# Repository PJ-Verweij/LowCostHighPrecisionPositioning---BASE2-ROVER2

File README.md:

# LowCostHighPrecisionPositioning - BASE2, ROVER2

Here you can find all 3D models (SolidWorks 2019), PCB designs (KiCad) and documentation for the BASE2 and ROVER2 which have been designed during the master thesis project of Peter Verweij. <br/><br/>

The aim of this project was to create a low cost high precision positioning system for Ghana. <br/>
The showcase and explanation of the project can be found in this [showcase movie](https://www.youtube.com/watch?v=F1svl4LCIXA&feature=youtu.be&ab_channel=PeterVerweij)<br/><br/>

For the Ublox GNSS receiver configuration I refer to the work of hcwinsemius and kriete on the [RTK_GNSS github page](https://github.com/hcwinsemius/RTK_GNSS)<br/><br/>

Finally, the files and explanation to add a GPRS cellular connection to the raspberry PI can be found here aswell.<br/><br/>

It has to be noted that this project is in a prototype state. There is still a lot to be desired. For example: the custom PCBs connect prototype breakoutboards, there are no indicator lights in the devices, etcetera.

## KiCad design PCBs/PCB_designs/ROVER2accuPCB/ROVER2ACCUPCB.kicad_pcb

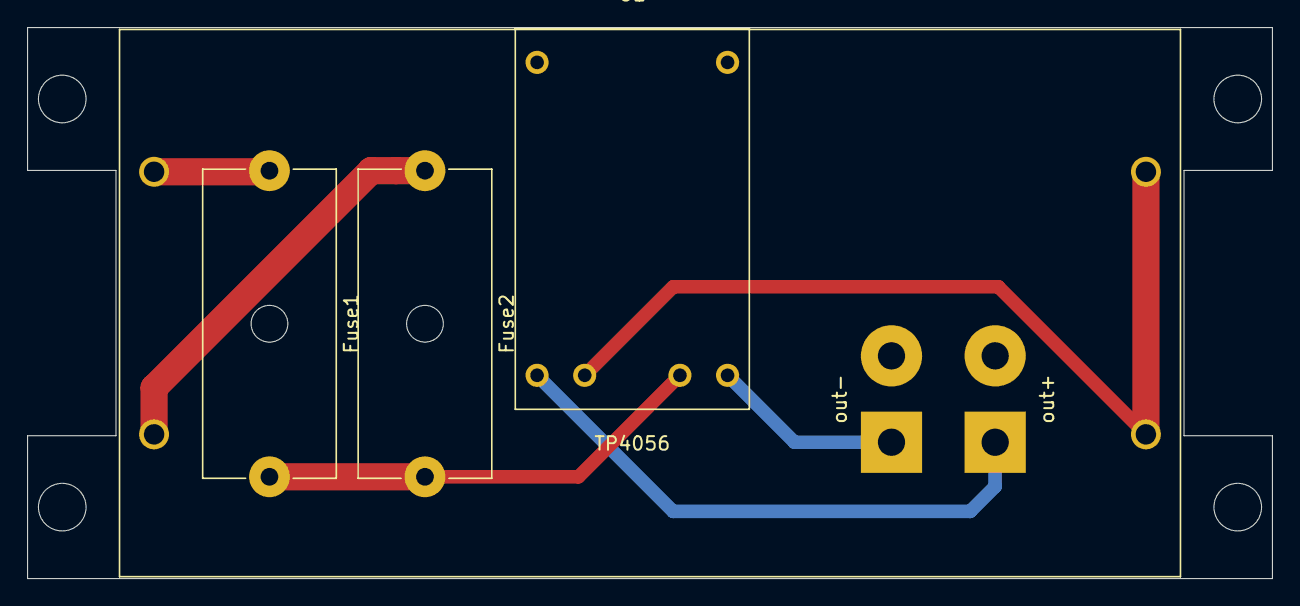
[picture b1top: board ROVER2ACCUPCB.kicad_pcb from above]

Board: 2 copper layers, 91.5 x 40.5 mm, 6 parts (0 on the bottom side), 6 nets.

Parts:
B1: Batteryholder2x18650
F1: Fuse1; Fuseholder_Cylinder-5x20mm_Schurter_0031_8201_Horizontal_Op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
F2: Fuse2; Fuseholder_Cylinder-5x20mm_Schurter_0031_8201_Horizontal_Op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
J1: out-; SolderWirePad_1x02_P7.62mm_Drill2mm
J2: out+; SolderWirePad_1x02_P7.62mm_Drill2mm
U1: TP4056

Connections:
unnamed: B1.1, F1.2
unnamed: B1.2, B1.4, U1.3
unnamed: B1.3, F2.2
unnamed: F1.1, F2.1, U1.2
unnamed: J1.1, U1.1
unnamed: J2.1, U1.4

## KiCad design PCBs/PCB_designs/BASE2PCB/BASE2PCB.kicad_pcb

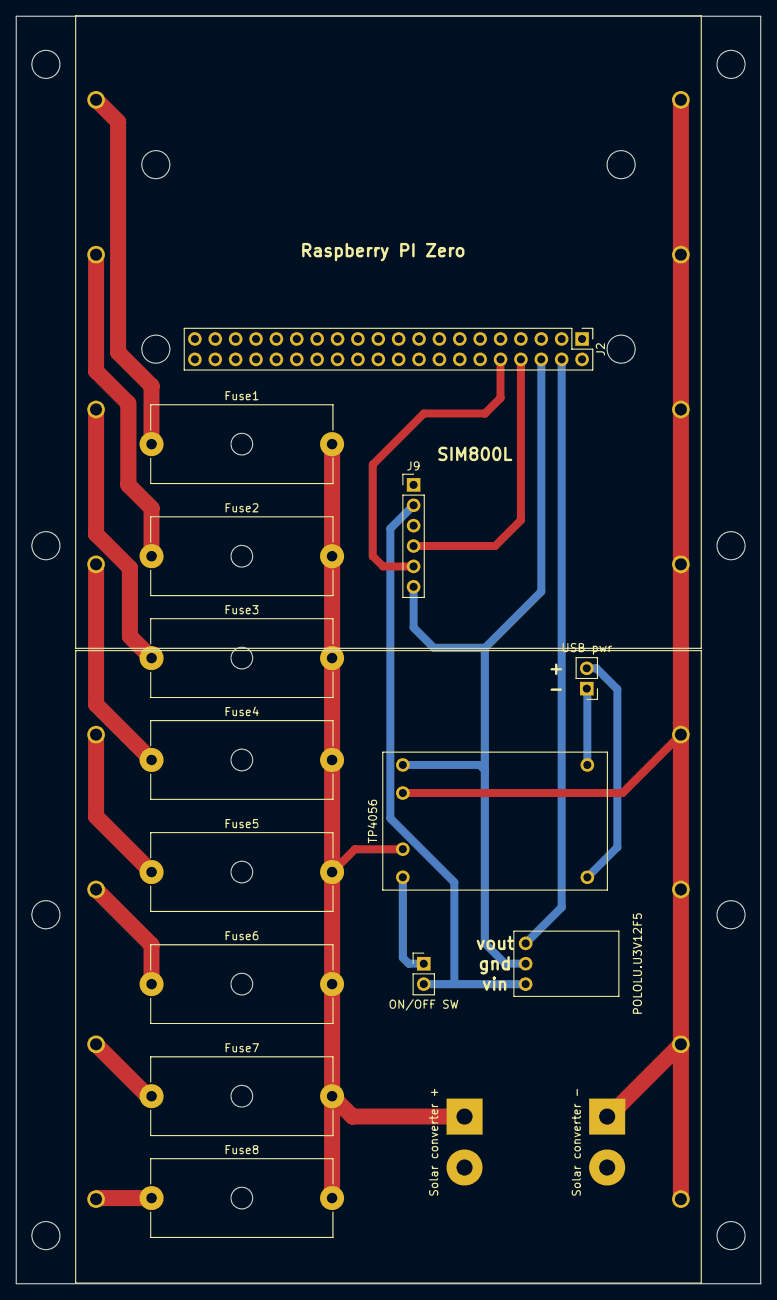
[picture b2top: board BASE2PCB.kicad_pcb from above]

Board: 2 copper layers, 92.8 x 158.0 mm, 18 parts (0 on the bottom side), 18 nets.

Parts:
F1: Fuse5; Fuseholder_Cylinder-5x20mm_Schurter_0031_8201_Horizontal_Op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
F2: Fuse6; Fuseholder_Cylinder-5x20mm_Schurter_0031_8201_Horizontal_Op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
F3: Fuse7; Fuseholder_Cylinder-5x20mm_Schurter_0031_8201_Horizontal_Op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
F4: Fuse8; Fuseholder_Cylinder-5x20mm_Schurter_0031_8201_Horizontal_Op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
F5: Fuse1; Fuseholder_Cylinder-5x20mm_Schurter_0031_8201_Horizontal_Op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
F6: Fuse2; Fuseholder_Cylinder-5x20mm_Schurter_0031_8201_Horizontal_Op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
F7: Fuse3; Fuseholder_Cylinder-5x20mm_Schurter_0031_8201_Horizontal_Op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
F8: Fuse4; Fuseholder_Cylinder-5x20mm_Schurter_0031_8201_Horizontal_Op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
J1: ON/OFF SW; PinHeader_1x02_P2.54mm_Vertical
J2: Conn_02x20_Odd_Even; PinHeader_2x20_P2.54mm_Vertical
J3: USB pwr; PinHeader_1x02_P2.54mm_Vertical
J4: Solar converter +; SolderWirePad_1x02_P7.62mm_Drill2mm
J6: Solar converter -; SolderWirePad_1x02_P7.62mm_Drill2mm
J9: Conn_01x06_Male; PinHeader_1x06_P2.54mm_Vertical
U1: POLOLU.U3V12F5; Pololu.U3V12F5
U2, U3: Batteryholder; Batteryholder4x18650
U4: TP4056

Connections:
unnamed: F1.1, F2.1, F3.1, F4.1, F5.1, F6.1, F7.1, F8.1, J4.1, U4.2
unnamed: F1.2, U2.1
unnamed: F2.2, U2.3
unnamed: F3.2, U2.5
unnamed: F4.2, U2.7
unnamed: F5.2, U3.1
unnamed: F6.2, U3.3
unnamed: F7.2, U3.5
unnamed: F8.2, U3.7
unnamed: J1.1, U4.1
unnamed: J1.2, J9.2, U1.1
unnamed: J2.4, U1.3
unnamed: J2.6, J9.6, U1.2, U4.4
unnamed: J2.8, J9.4
unnamed: J2.10, J9.5
unnamed: J3.1, U4.5
unnamed: J3.2, U4.6
unnamed: J6.1, U2.2, U2.4, U2.6, U2.8, U3.2, U3.4, U3.6, U3.8, U4.3

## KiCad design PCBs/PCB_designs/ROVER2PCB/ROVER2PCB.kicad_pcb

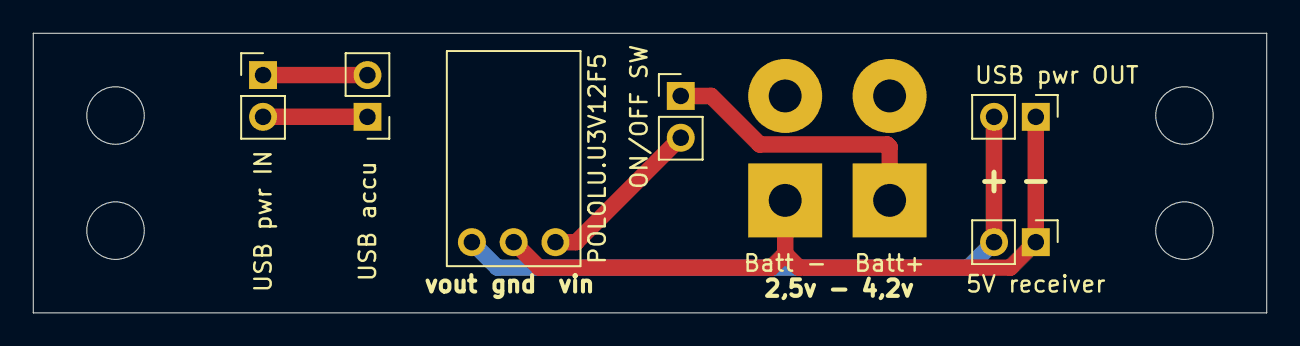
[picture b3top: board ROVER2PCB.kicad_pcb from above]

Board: 2 copper layers, 75.0 x 17.0 mm, 8 parts (0 on the bottom side), 6 nets.

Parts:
J1: Batt+; SolderWirePad_1x02_P7.62mm_Drill2mm
J2: Batt -; SolderWirePad_1x02_P7.62mm_Drill2mm
J3: USB accu; PinHeader_1x02_P2.54mm_Vertical
J4: USB pwr IN; PinHeader_1x02_P2.54mm_Vertical
J5: USB pwr OUT; PinHeader_1x02_P2.54mm_Vertical
J6: 5V receiver; PinHeader_1x02_P2.54mm_Vertical
J7: ON/OFF SW; PinHeader_1x02_P2.54mm_Vertical
U1: POLOLU.U3V12F5; Pololu.U3V12F5

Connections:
unnamed: J1.1, J7.1
unnamed: J2.1, J5.1, J6.1, U1.2
unnamed: J3.1, J4.2
unnamed: J3.2, J4.1
unnamed: J5.2, J6.2, U1.3
unnamed: J7.2, U1.1

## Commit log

2020-09-22 Initial upload
2020-09-22 systemfiles removed
